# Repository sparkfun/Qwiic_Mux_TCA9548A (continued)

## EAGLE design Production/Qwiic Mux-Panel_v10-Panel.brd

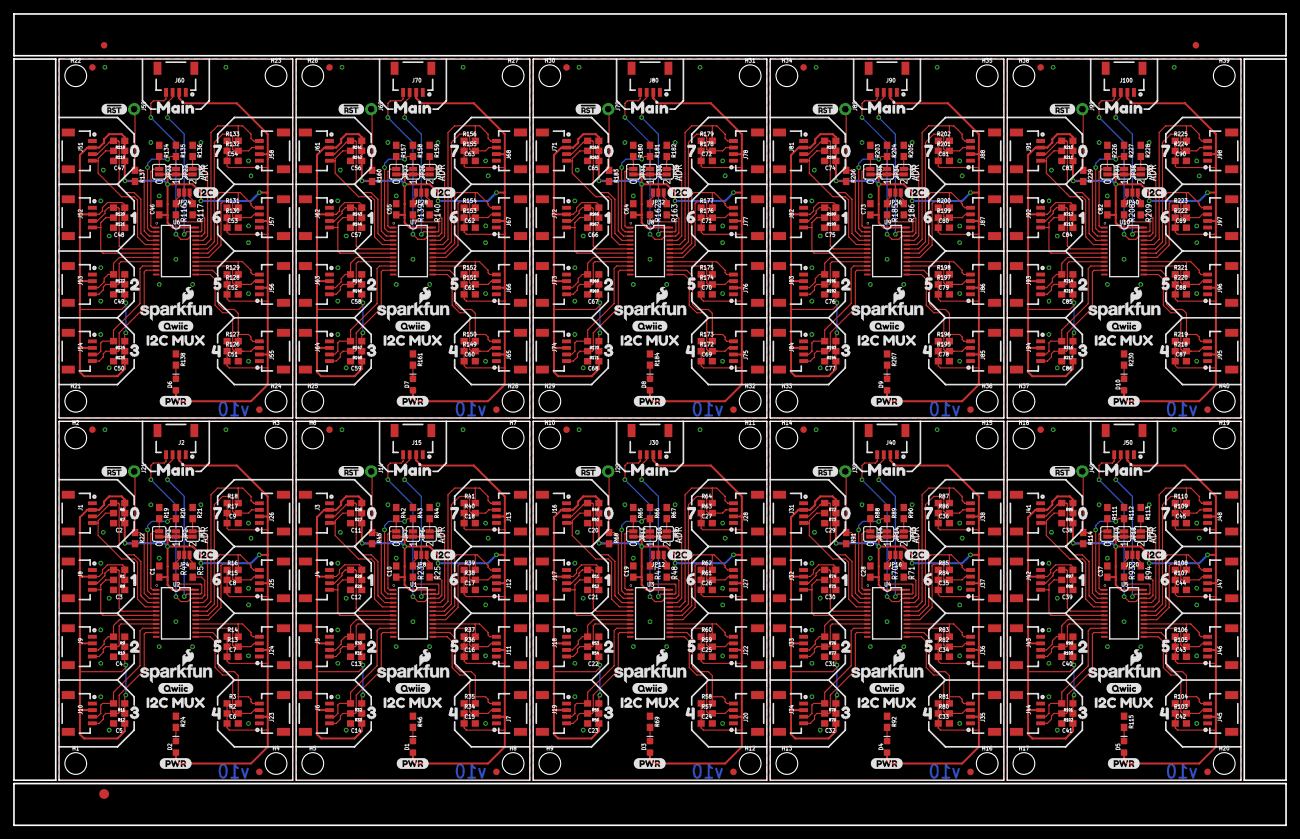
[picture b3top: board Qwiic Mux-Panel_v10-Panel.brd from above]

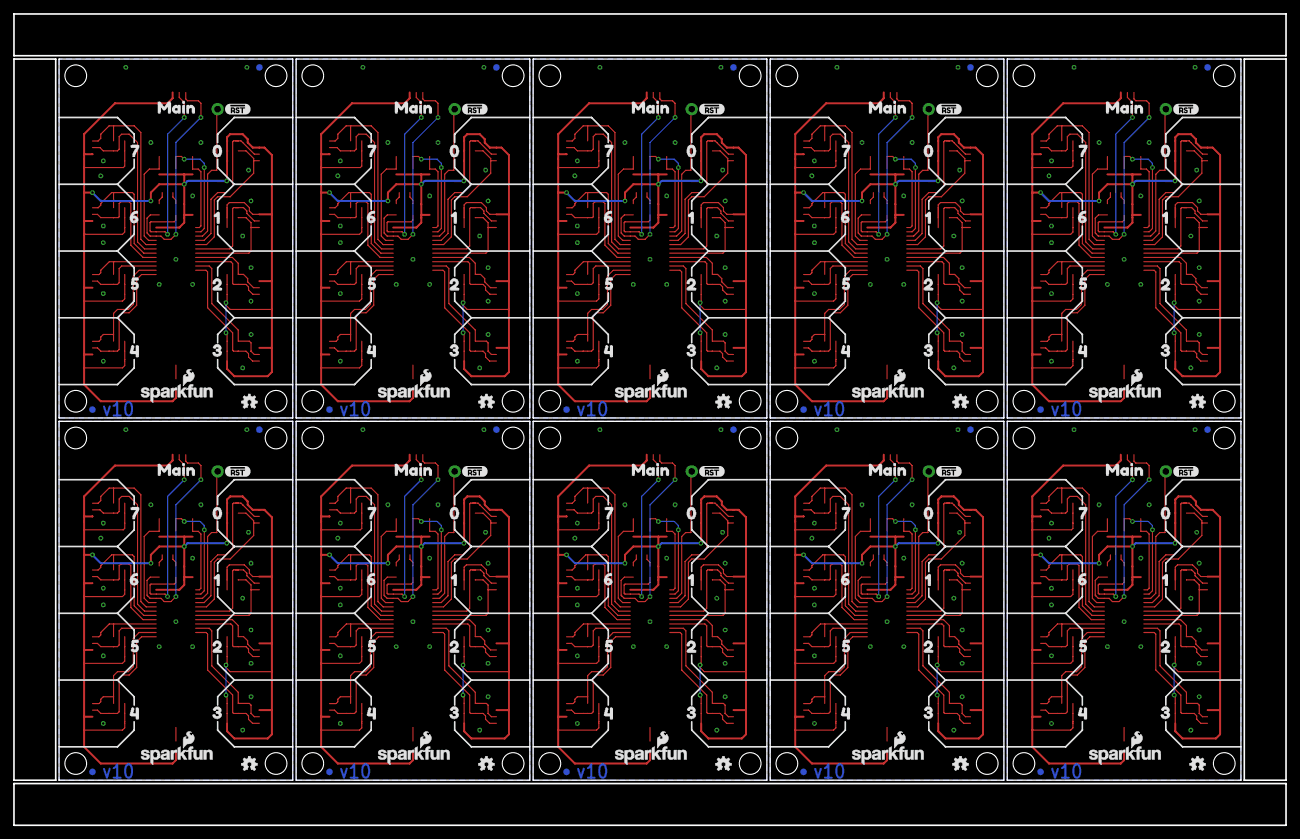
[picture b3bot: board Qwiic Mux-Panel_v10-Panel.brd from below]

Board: 2 copper layers, 193.5 x 123.4 mm, 833 parts (140 on the bottom side), 270 nets.

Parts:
C1, C10, C19, C28, C37, C46, C55, C64, C73, C82: 0.1uF; 0603
C2, C3, C4, C5, C6, C7, C8, C9, C11, C12, C13, C14, C15, C16, C17, C18, C20, C21, C22, C23, C24, C25, C26, C27, C29, C30, C31, C32, C33, C34, C35, C36, C38, C39, C40, C41, C42, C43, C44, C45, C47, C48, C49, C50, C51, C52, C53, C54, C56, C57, C58, C59, C60, C61, C62, C63, C65, C66, C67, C68, C69, C70, C71, C72, C74, C75, C76, C77, C78, C79, C80, C81, C83, C84, C85, C86, C87, C88, C89, C90: 1.0uF; 0603
D1, D2, D3, D4, D5, D6, D7, D8, D9, D10: RED; LED-0603
E$1, E$2: FIDUCIAL-1X2
E$3: FIDUCIAL-1.5X3
FD1, FD2, FD3, FD4, FD5, FD6, FD7, FD8, FD9, FD10, FD11, FD12, FD13, FD14, FD15, FD16, FD17, FD18, FD19, FD20, FD21, FD22, FD23, FD24, FD25, FD26, FD27, FD28, FD29, FD30, FD31, FD32, FD33, FD34, FD35, FD36, FD37, FD38, FD39, FD40: FIDUCIAL1X2; FIDUCIAL-1X2
H1, H2, H3, H4, H5, H6, H7, H8, H9, H10, H11, H12, H13, H14, H15, H16, H17, H18, H19, H20, H21, H22, H23, H24, H25, H26, H27, H28, H29, H30, H31, H32, H33, H34, H35, H36, H37, H38, H39, H40: STAND-OFF
J1, J3, J4, J5, J6, J7, J8, J9, J10, J11, J12, J13, J16, J17, J18, J19, J20, J22, J23, J24, J25, J26, J27, J28, J31, J32, J33, J34, J35, J36, J37, J38, J41, J42, J43, J44, J45, J46, J47, J48, J51, J52, J53, J54, J55, J56, J57, J58, J61, J62, J63, J64, J65, J66, J67, J68, J71, J72, J73, J74, J75, J76, J77, J78, J81, J82, J83, J84, J85, J86, J87, J88, J91, J92, J93, J94, J95, J96, J97, J98: 1X04_1MM_RA
J2, J15, J30, J40, J50, J60, J70, J80, J90, J100: SMD; 1X04_1MM_RA
J14, J21, J29, J39, J49, J59, J69, J79, J89, J99: 1X01_NO_SILK
JP1, JP2, JP3, JP5, JP6, JP7, JP9, JP10, JP11, JP13, JP14, JP15, JP17, JP18, JP19, JP21, JP22, JP23, JP25, JP26, JP27, JP29, JP30, JP31, JP33, JP34, JP35, JP37, JP38, JP39: SMT-JUMPER_2_NO_SILK
JP4, JP8, JP12, JP16, JP20, JP24, JP28, JP32, JP36, JP40: JUMPER-SMT_3_2-NC_PASTE_NO-SILK; SMT-JUMPER_3_2-NC_PASTE_NO-SILK
LOGO1, LOGO2, LOGO3, LOGO4, LOGO5, LOGO6, LOGO7, LOGO8, LOGO9, LOGO10: OSHW-LOGOMINI; OSHW-LOGO-MINI
R1, R2, R3, R4, R5, R6, R7, R8, R9, R10, R11, R12, R13, R14, R15, R16, R17, R18, R23, R25, R26, R27, R28, R29, R30, R31, R32, R33, R34, R35, R36, R37, R38, R39, R40, R41, R47, R48, R49, R50, R51, R52, R53, R54, R55, R56, R57, R58, R59, R60, R61, R62, R63, R64, R70, R71, R72, R73, R74, R75, R76, R77, R78, R79, R80, R81, R82, R83, R84, R85, R86, R87, R93, R94, R95, R96, R97, R98, R99, R100, R101, R102, R103, R104, R105, R106, R107, R108, R109, R110, R116, R117, R118, R119, R120, R121, R122, R123, R124, R125, R126, R127, R128, R129, R130, R131, R132, R133, R139, R140, R141, R142, R143, R144, R145, R146, R147, R148, R149, R150, R151, R152, R153, R154, R155, R156, R162, R163, R164, R165, R166, R167, R168, R169, R170, R171, R172, R173, R174, R175, R176, R177, R178, R179, R185, R186, R187, R188, R189, R190, R191, R192, R193, R194, R195, R196, R197, R198, R199, R200, R201, R202, R208, R209, R210, R211, R212, R213, R214, R215, R216, R217, R218, R219, R220, R221, R222, R223, R224, R225: 4.7k; 0603
R19, R20, R21, R22, R42, R43, R44, R45, R65, R66, R67, R68, R88, R89, R90, R91, R111, R112, R113, R114, R134, R135, R136, R137, R157, R158, R159, R160, R180, R181, R182, R183, R203, R204, R205, R206, R226, R227, R228, R229: 10k; 0603
R24, R46, R69, R92, R115, R138, R161, R184, R207, R230: 1k; 0603
U1, U2, U3, U4, U5, U6, U7, U8, U9, U10: PCA9548A; TSSOP28
U$1, U$2, U$27, U$28, U$53, U$54, U$79, U$80, U$105, U$106, U$131, U$132, U$157, U$158, U$183, U$184, U$209, U$210, U$235, U$236: SFE_LOGO_NAME_FLAME.1_INCH; SFE_LOGO_NAME_FLAME_.1
U$3, U$29, U$55, U$81, U$107, U$133, U$159, U$185, U$211, U$237: (PWR)
U$4, U$30, U$56, U$82, U$108, U$134, U$160, U$186, U$212, U$238: (QWIIC)
U$5, U$31, U$57, U$83, U$109, U$135, U$161, U$187, U$213, U$239: (I2C)
U$6, U$12, U$32, U$43, U$58, U$69, U$84, U$95, U$110, U$121, U$136, U$147, U$162, U$173, U$188, U$199, U$214, U$225, U$240, U$251: 00
U$7, U$18, U$37, U$44, U$63, U$70, U$89, U$96, U$115, U$122, U$141, U$148, U$167, U$174, U$193, U$200, U$219, U$226, U$245, U$252: 11
U$8, U$19, U$38, U$45, U$64, U$71, U$90, U$97, U$116, U$123, U$142, U$149, U$168, U$175, U$194, U$201, U$220, U$227, U$246, U$253: 22
U$9, U$20, U$39, U$46, U$65, U$72, U$91, U$98, U$117, U$124, U$143, U$150, U$169, U$176, U$195, U$202, U$221, U$228, U$247, U$254: 33
U$10, U$21, U$33, U$47, U$59, U$73, U$85, U$99, U$111, U$125, U$137, U$151, U$163, U$177, U$189, U$203, U$215, U$229, U$241, U$255: 44
U$11, U$22, U$34, U$48, U$60, U$74, U$86, U$100, U$112, U$126, U$138, U$152, U$164, U$178, U$190, U$204, U$216, U$230, U$242, U$256: 55
U$13, U$24, U$35, U$50, U$61, U$76, U$87, U$102, U$113, U$128, U$139, U$154, U$165, U$180, U$191, U$206, U$217, U$232, U$243, U$258: 77
U$14, U$26, U$36, U$52, U$62, U$78, U$88, U$104, U$114, U$130, U$140, U$156, U$166, U$182, U$192, U$208, U$218, U$234, U$244, U$260: #RST10
U$15, U$40, U$66, U$92, U$118, U$144, U$170, U$196, U$222, U$248: I2C_MUX8
U$16, U$25, U$41, U$51, U$67, U$77, U$93, U$103, U$119, U$129, U$145, U$155, U$171, U$181, U$197, U$207, U$223, U$233, U$249, U$259: MAIN0
U$17, U$23, U$42, U$49, U$68, U$75, U$94, U$101, U$120, U$127, U$146, U$153, U$172, U$179, U$198, U$205, U$224, U$231, U$250, U$257: 61

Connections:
3.3V: C1.1, C2.1, C3.1, C4.1, C5.1, C6.1, C7.1, C8.1, C9.1, D2.A, J1.2, J2.2, J8.2, J9.2, J10.2, J23.2, J24.2, J25.2, J26.2, JP1.2, JP2.2, JP3.2, JP4.2, R1.1, R2.1, R3.1, R6.1, R7.1, R8.1, R9.1, R10.1, R11.1, R12.1, R13.1, R14.1, R15.1, R16.1, R17.1, R18.1, R22.2, U2.24
3.3V1: C10.1, C11.1, C12.1, C13.1, C14.1, C15.1, C16.1, C17.1, C18.1, D1.A, J3.2, J4.2, J5.2, J6.2, J7.2, J11.2, J12.2, J13.2, J15.2, JP5.2, JP6.2, JP7.2, JP8.2, R26.1, R27.1, R28.1, R29.1, R30.1, R31.1, R32.1, R33.1, R34.1, R35.1, R36.1, R37.1, R38.1, R39.1, R40.1, R41.1, R45.2, U1.24
3.3V2: C19.1, C20.1, C21.1, C22.1, C23.1, C24.1, C25.1, C26.1, C27.1, D3.A, J16.2, J17.2, J18.2, J19.2, J20.2, J22.2, J27.2, J28.2, J30.2, JP9.2, JP10.2, JP11.2, JP12.2, R49.1, R50.1, R51.1, R52.1, R53.1, R54.1, R55.1, R56.1, R57.1, R58.1, R59.1, R60.1, R61.1, R62.1, R63.1, R64.1, R68.2, U3.24
3.3V3: C28.1, C29.1, C30.1, C31.1, C32.1, C33.1, C34.1, C35.1, C36.1, D4.A, J31.2, J32.2, J33.2, J34.2, J35.2, J36.2, J37.2, J38.2, J40.2, JP13.2, JP14.2, JP15.2, JP16.2, R72.1, R73.1, R74.1, R75.1, R76.1, R77.1, R78.1, R79.1, R80.1, R81.1, R82.1, R83.1, R84.1, R85.1, R86.1, R87.1, R91.2, U4.24
3.3V4: C37.1, C38.1, C39.1, C40.1, C41.1, C42.1, C43.1, C44.1, C45.1, D5.A, J41.2, J42.2, J43.2, J44.2, J45.2, J46.2, J47.2, J48.2, J50.2, JP17.2, JP18.2, JP19.2, JP20.2, R95.1, R96.1, R97.1, R98.1, R99.1, R100.1, R101.1, R102.1, R103.1, R104.1, R105.1, R106.1, R107.1, R108.1, R109.1, R110.1, R114.2, U5.24
3.3V5: C46.1, C47.1, C48.1, C49.1, C50.1, C51.1, C52.1, C53.1, C54.1, D6.A, J51.2, J52.2, J53.2, J54.2, J55.2, J56.2, J57.2, J58.2, J60.2, JP21.2, JP22.2, JP23.2, JP24.2, R118.1, R119.1, R120.1, R121.1, R122.1, R123.1, R124.1, R125.1, R126.1, R127.1, R128.1, R129.1, R130.1, R131.1, R132.1, R133.1, R137.2, U6.24
3.3V6: C55.1, C56.1, C57.1, C58.1, C59.1, C60.1, C61.1, C62.1, C63.1, D7.A, J61.2, J62.2, J63.2, J64.2, J65.2, J66.2, J67.2, J68.2, J70.2, JP25.2, JP26.2, JP27.2, JP28.2, R141.1, R142.1, R143.1, R144.1, R145.1, R146.1, R147.1, R148.1, R149.1, R150.1, R151.1, R152.1, R153.1, R154.1, R155.1, R156.1, R160.2, U7.24
3.3V7: C64.1, C65.1, C66.1, C67.1, C68.1, C69.1, C70.1, C71.1, C72.1, D8.A, J71.2, J72.2, J73.2, J74.2, J75.2, J76.2, J77.2, J78.2, J80.2, JP29.2, JP30.2, JP31.2, JP32.2, R164.1, R165.1, R166.1, R167.1, R168.1, R169.1, R170.1, R171.1, R172.1, R173.1, R174.1, R175.1, R176.1, R177.1, R178.1, R179.1, R183.2, U8.24
3.3V8: C73.1, C74.1, C75.1, C76.1, C77.1, C78.1, C79.1, C80.1, C81.1, D9.A, J81.2, J82.2, J83.2, J84.2, J85.2, J86.2, J87.2, J88.2, J90.2, JP33.2, JP34.2, JP35.2, JP36.2, R187.1, R188.1, R189.1, R190.1, R191.1, R192.1, R193.1, R194.1, R195.1, R196.1, R197.1, R198.1, R199.1, R200.1, R201.1, R202.1, R206.2, U9.24
3.3V9: C82.1, C83.1, C84.1, C85.1, C86.1, C87.1, C88.1, C89.1, C90.1, D10.A, J91.2, J92.2, J93.2, J94.2, J95.2, J96.2, J97.2, J98.2, J100.2, JP37.2, JP38.2, JP39.2, JP40.2, R210.1, R211.1, R212.1, R213.1, R214.1, R215.1, R216.1, R217.1, R218.1, R219.1, R220.1, R221.1, R222.1, R223.1, R224.1, R225.1, R229.2, U10.24
!RST: J21.1, R22.1, U2.3
!RST1: J14.1, R45.1, U1.3
!RST2: J29.1, R68.1, U3.3
!RST3: J39.1, R91.1, U4.3
!RST4: J49.1, R114.1, U5.3
!RST5: J59.1, R137.1, U6.3
!RST6: J69.1, R160.1, U7.3
!RST7: J79.1, R183.1, U8.3
!RST8: J89.1, R206.1, U9.3
!RST9: J99.1, R229.1, U10.3
ADR0: JP3.1, R19.2, U2.1
ADR1: JP2.1, R20.2, U2.2
ADR2: JP1.1, R21.2, U2.21
ADR3: JP6.1, R43.2, U1.2
ADR4: JP7.1, R42.2, U1.1
ADR5: JP5.1, R44.2, U1.21
ADR6: JP10.1, R66.2, U3.2
ADR7: JP11.1, R65.2, U3.1
ADR8: JP9.1, R67.2, U3.21
ADR9: JP14.1, R89.2, U4.2
ADR10: JP15.1, R88.2, U4.1
ADR11: JP13.1, R90.2, U4.21
ADR12: JP18.1, R112.2, U5.2
ADR13: JP19.1, R111.2, U5.1
ADR14: JP17.1, R113.2, U5.21
ADR15: JP22.1, R135.2, U6.2
ADR16: JP23.1, R134.2, U6.1
ADR17: JP21.1, R136.2, U6.21
ADR18: JP26.1, R158.2, U7.2
ADR19: JP27.1, R157.2, U7.1
ADR20: JP25.1, R159.2, U7.21
ADR21: JP30.1, R181.2, U8.2
ADR22: JP31.1, R180.2, U8.1
ADR23: JP29.1, R182.2, U8.21
ADR24: JP34.1, R204.2, U9.2
ADR25: JP35.1, R203.2, U9.1
ADR26: JP33.1, R205.2, U9.21
ADR27: JP38.1, R227.2, U10.2
ADR28: JP39.1, R226.2, U10.1
ADR29: JP37.1, R228.2, U10.21
GND: C1.2, C2.2, C3.2, C4.2, C5.2, C6.2, C7.2, C8.2, C9.2, J1.1, J2.1, J8.1, J9.1, J10.1, J23.1, J24.1, J25.1, J26.1, R19.1, R20.1, R21.1, R24.1, U2.12
GND1: C10.2, C11.2, C12.2, C13.2, C14.2, C15.2, C16.2, C17.2, C18.2, J3.1, J4.1, J5.1, J6.1, J7.1, J11.1, J12.1, J13.1, J15.1, R42.1, R43.1, R44.1, R46.1, U1.12
GND2: C19.2, C20.2, C21.2, C22.2, C23.2, C24.2, C25.2, C26.2, C27.2, J16.1, J17.1, J18.1, J19.1, J20.1, J22.1, J27.1, J28.1, J30.1, R65.1, R66.1, R67.1, R69.1, U3.12
GND3: C28.2, C29.2, C30.2, C31.2, C32.2, C33.2, C34.2, C35.2, C36.2, J31.1, J32.1, J33.1, J34.1, J35.1, J36.1, J37.1, J38.1, J40.1, R88.1, R89.1, R90.1, R92.1, U4.12
GND4: C37.2, C38.2, C39.2, C40.2, C41.2, C42.2, C43.2, C44.2, C45.2, J41.1, J42.1, J43.1, J44.1, J45.1, J46.1, J47.1, J48.1, J50.1, R111.1, R112.1, R113.1, R115.1, U5.12
GND5: C46.2, C47.2, C48.2, C49.2, C50.2, C51.2, C52.2, C53.2, C54.2, J51.1, J52.1, J53.1, J54.1, J55.1, J56.1, J57.1, J58.1, J60.1, R134.1, R135.1, R136.1, R138.1, U6.12
GND6: C55.2, C56.2, C57.2, C58.2, C59.2, C60.2, C61.2, C62.2, C63.2, J61.1, J62.1, J63.1, J64.1, J65.1, J66.1, J67.1, J68.1, J70.1, R157.1, R158.1, R159.1, R161.1, U7.12
GND7: C64.2, C65.2, C66.2, C67.2, C68.2, C69.2, C70.2, C71.2, C72.2, J71.1, J72.1, J73.1, J74.1, J75.1, J76.1, J77.1, J78.1, J80.1, R180.1, R181.1, R182.1, R184.1, U8.12
GND8: C73.2, C74.2, C75.2, C76.2, C77.2, C78.2, C79.2, C80.2, C81.2, J81.1, J82.1, J83.1, J84.1, J85.1, J86.1, J87.1, J88.1, J90.1, R203.1, R204.1, R205.1, R207.1, U9.12
GND9: C82.2, C83.2, C84.2, C85.2, C86.2, C87.2, C88.2, C89.2, C90.2, J91.1, J92.1, J93.1, J94.1, J95.1, J96.1, J97.1, J98.1, J100.1, R226.1, R227.1, R228.1, R230.1, U10.12
MAIN_SCL: J2.4, R5.2, U2.22
MAIN_SCL1: J15.4, R25.2, U1.22
MAIN_SCL2: J30.4, R48.2, U3.22
MAIN_SCL3: J40.4, R71.2, U4.22
MAIN_SCL4: J50.4, R94.2, U5.22
MAIN_SCL5: J60.4, R117.2, U6.22
MAIN_SCL6: J70.4, R140.2, U7.22
MAIN_SCL7: J80.4, R163.2, U8.22
MAIN_SCL8: J90.4, R186.2, U9.22
MAIN_SCL9: J100.4, R209.2, U10.22
MAIN_SDA: J2.3, R4.2, U2.23
MAIN_SDA1: J15.3, R23.2, U1.23
MAIN_SDA2: J30.3, R47.2, U3.23
MAIN_SDA3: J40.3, R70.2, U4.23
MAIN_SDA4: J50.3, R93.2, U5.23
MAIN_SDA5: J60.3, R116.2, U6.23
MAIN_SDA6: J70.3, R139.2, U7.23
MAIN_SDA7: J80.3, R162.2, U8.23
MAIN_SDA8: J90.3, R185.2, U9.23
MAIN_SDA9: J100.3, R208.2, U10.23
unnamed: D2.C, R24.2
unnamed: JP4.3, R4.1
unnamed: JP4.1, R5.1
unnamed: D1.C, R46.2
unnamed: JP8.3, R23.1
unnamed: JP8.1, R25.1
unnamed: D3.C, R69.2
unnamed: JP12.3, R47.1
unnamed: JP12.1, R48.1
unnamed: D4.C, R92.2
unnamed: JP16.3, R70.1
unnamed: JP16.1, R71.1
unnamed: D5.C, R115.2
unnamed: JP20.3, R93.1
unnamed: JP20.1, R94.1
unnamed: D6.C, R138.2
unnamed: JP24.3, R116.1
unnamed: JP24.1, R117.1
unnamed: D7.C, R161.2
unnamed: JP28.3, R139.1
unnamed: JP28.1, R140.1
unnamed: D8.C, R184.2
unnamed: JP32.3, R162.1
unnamed: JP32.1, R163.1
unnamed: D9.C, R207.2
unnamed: JP36.3, R185.1
unnamed: JP36.1, R186.1
unnamed: D10.C, R230.2
unnamed: JP40.3, R208.1
unnamed: JP40.1, R209.1
SCL0: J1.4, R7.2, U2.5
SCL1: J8.4, R8.2, U2.7
SCL2: J9.4, R10.2, U2.9
SCL3: J10.4, R12.2, U2.11
SCL4: J23.4, R3.2, U2.14
SCL5: J24.4, R14.2, U2.16
SCL6: J25.4, R16.2, U2.18
SCL7: J26.4, R18.2, U2.20
SCL8: J3.4, R27.2, U1.5
SCL9: J4.4, R29.2, U1.7
SCL10: J6.4, R33.2, U1.11
SCL11: J7.4, R35.2, U1.14
SCL12: J11.4, R37.2, U1.16
SCL13: J12.4, R39.2, U1.18
SCL14: J13.4, R41.2, U1.20
SCL15: J5.4, R31.2, U1.9
SCL16: J16.4, R50.2, U3.5
SCL17: J17.4, R52.2, U3.7
SCL18: J19.4, R56.2, U3.11
SCL19: J20.4, R58.2, U3.14
SCL20: J22.4, R60.2, U3.16
SCL21: J27.4, R62.2, U3.18
SCL22: J28.4, R64.2, U3.20
SCL23: J18.4, R54.2, U3.9
SCL24: J31.4, R73.2, U4.5
SCL25: J32.4, R75.2, U4.7
SCL26: J34.4, R79.2, U4.11
SCL27: J35.4, R81.2, U4.14
SCL28: J36.4, R83.2, U4.16
SCL29: J37.4, R85.2, U4.18
SCL30: J38.4, R87.2, U4.20
SCL31: J33.4, R77.2, U4.9
SCL32: J41.4, R96.2, U5.5
SCL33: J42.4, R98.2, U5.7
SCL34: J44.4, R102.2, U5.11
SCL35: J45.4, R104.2, U5.14
SCL36: J46.4, R106.2, U5.16
SCL37: J47.4, R108.2, U5.18
SCL38: J48.4, R110.2, U5.20
SCL39: J43.4, R100.2, U5.9
SCL40: J51.4, R119.2, U6.5
SCL41: J52.4, R121.2, U6.7
SCL42: J54.4, R125.2, U6.11
SCL43: J55.4, R127.2, U6.14
SCL44: J56.4, R129.2, U6.16
SCL45: J57.4, R131.2, U6.18
SCL46: J58.4, R133.2, U6.20
SCL47: J53.4, R123.2, U6.9
SCL48: J61.4, R142.2, U7.5
SCL49: J62.4, R144.2, U7.7
SCL50: J64.4, R148.2, U7.11
SCL51: J65.4, R150.2, U7.14
SCL52: J66.4, R152.2, U7.16
SCL53: J67.4, R154.2, U7.18
SCL54: J68.4, R156.2, U7.20
SCL55: J63.4, R146.2, U7.9
SCL56: J71.4, R165.2, U8.5
SCL57: J72.4, R167.2, U8.7
SCL58: J74.4, R171.2, U8.11
SCL59: J75.4, R173.2, U8.14
SCL60: J76.4, R175.2, U8.16
SCL61: J77.4, R177.2, U8.18
SCL62: J78.4, R179.2, U8.20
SCL63: J73.4, R169.2, U8.9
SCL64: J81.4, R188.2, U9.5
SCL65: J82.4, R190.2, U9.7
SCL66: J84.4, R194.2, U9.11
SCL67: J85.4, R196.2, U9.14
SCL68: J86.4, R198.2, U9.16
SCL69: J87.4, R200.2, U9.18
SCL70: J88.4, R202.2, U9.20
SCL71: J83.4, R192.2, U9.9
SCL72: J91.4, R211.2, U10.5
SCL73: J92.4, R213.2, U10.7
SCL74: J94.4, R217.2, U10.11
SCL75: J95.4, R219.2, U10.14
SCL76: J96.4, R221.2, U10.16
SCL77: J97.4, R223.2, U10.18
SCL78: J98.4, R225.2, U10.20
SCL79: J93.4, R215.2, U10.9
SDA0: J1.3, R6.2, U2.4
SDA1: J8.3, R1.2, U2.6
SDA2: J9.3, R9.2, U2.8
SDA3: J10.3, R11.2, U2.10
SDA4: J23.3, R2.2, U2.13
SDA5: J24.3, R13.2, U2.15
SDA6: J25.3, R15.2, U2.17
SDA7: J26.3, R17.2, U2.19
SDA8: J3.3, R26.2, U1.4
SDA9: J4.3, R28.2, U1.6
SDA10: J6.3, R32.2, U1.10
SDA11: J7.3, R34.2, U1.13
SDA12: J11.3, R36.2, U1.15
SDA13: J13.3, R40.2, U1.19
SDA14: J12.3, R38.2, U1.17
SDA15: J5.3, R30.2, U1.8
SDA16: J16.3, R49.2, U3.4
SDA17: J17.3, R51.2, U3.6
SDA18: J19.3, R55.2, U3.10
SDA19: J20.3, R57.2, U3.13
SDA20: J22.3, R59.2, U3.15
SDA21: J28.3, R63.2, U3.19
SDA22: J27.3, R61.2, U3.17
SDA23: J18.3, R53.2, U3.8
SDA24: J31.3, R72.2, U4.4
SDA25: J32.3, R74.2, U4.6
SDA26: J34.3, R78.2, U4.10
SDA27: J35.3, R80.2, U4.13
SDA28: J36.3, R82.2, U4.15
SDA29: J38.3, R86.2, U4.19
SDA30: J37.3, R84.2, U4.17
SDA31: J33.3, R76.2, U4.8
SDA32: J41.3, R95.2, U5.4
SDA33: J42.3, R97.2, U5.6
SDA34: J44.3, R101.2, U5.10
SDA35: J45.3, R103.2, U5.13
SDA36: J46.3, R105.2, U5.15
SDA37: J48.3, R109.2, U5.19
SDA38: J47.3, R107.2, U5.17
SDA39: J43.3, R99.2, U5.8
SDA40: J51.3, R118.2, U6.4
SDA41: J52.3, R120.2, U6.6
SDA42: J54.3, R124.2, U6.10
SDA43: J55.3, R126.2, U6.13
SDA44: J56.3, R128.2, U6.15
SDA45: J58.3, R132.2, U6.19
SDA46: J57.3, R130.2, U6.17
SDA47: J53.3, R122.2, U6.8
SDA48: J61.3, R141.2, U7.4
SDA49: J62.3, R143.2, U7.6
SDA50: J64.3, R147.2, U7.10
SDA51: J65.3, R149.2, U7.13
SDA52: J66.3, R151.2, U7.15
SDA53: J68.3, R155.2, U7.19
SDA54: J67.3, R153.2, U7.17
SDA55: J63.3, R145.2, U7.8
SDA56: J71.3, R164.2, U8.4
SDA57: J72.3, R166.2, U8.6
SDA58: J74.3, R170.2, U8.10
SDA59: J75.3, R172.2, U8.13
SDA60: J76.3, R174.2, U8.15
SDA61: J78.3, R178.2, U8.19
SDA62: J77.3, R176.2, U8.17
SDA63: J73.3, R168.2, U8.8
SDA64: J81.3, R187.2, U9.4
SDA65: J82.3, R189.2, U9.6
SDA66: J84.3, R193.2, U9.10
SDA67: J85.3, R195.2, U9.13
SDA68: J86.3, R197.2, U9.15
SDA69: J88.3, R201.2, U9.19
SDA70: J87.3, R199.2, U9.17
SDA71: J83.3, R191.2, U9.8
SDA72: J91.3, R210.2, U10.4
SDA73: J92.3, R212.2, U10.6
SDA74: J94.3, R216.2, U10.10
SDA75: J95.3, R218.2, U10.13
SDA76: J96.3, R220.2, U10.15
SDA77: J98.3, R224.2, U10.19
SDA78: J97.3, R222.2, U10.17
SDA79: J93.3, R214.2, U10.8

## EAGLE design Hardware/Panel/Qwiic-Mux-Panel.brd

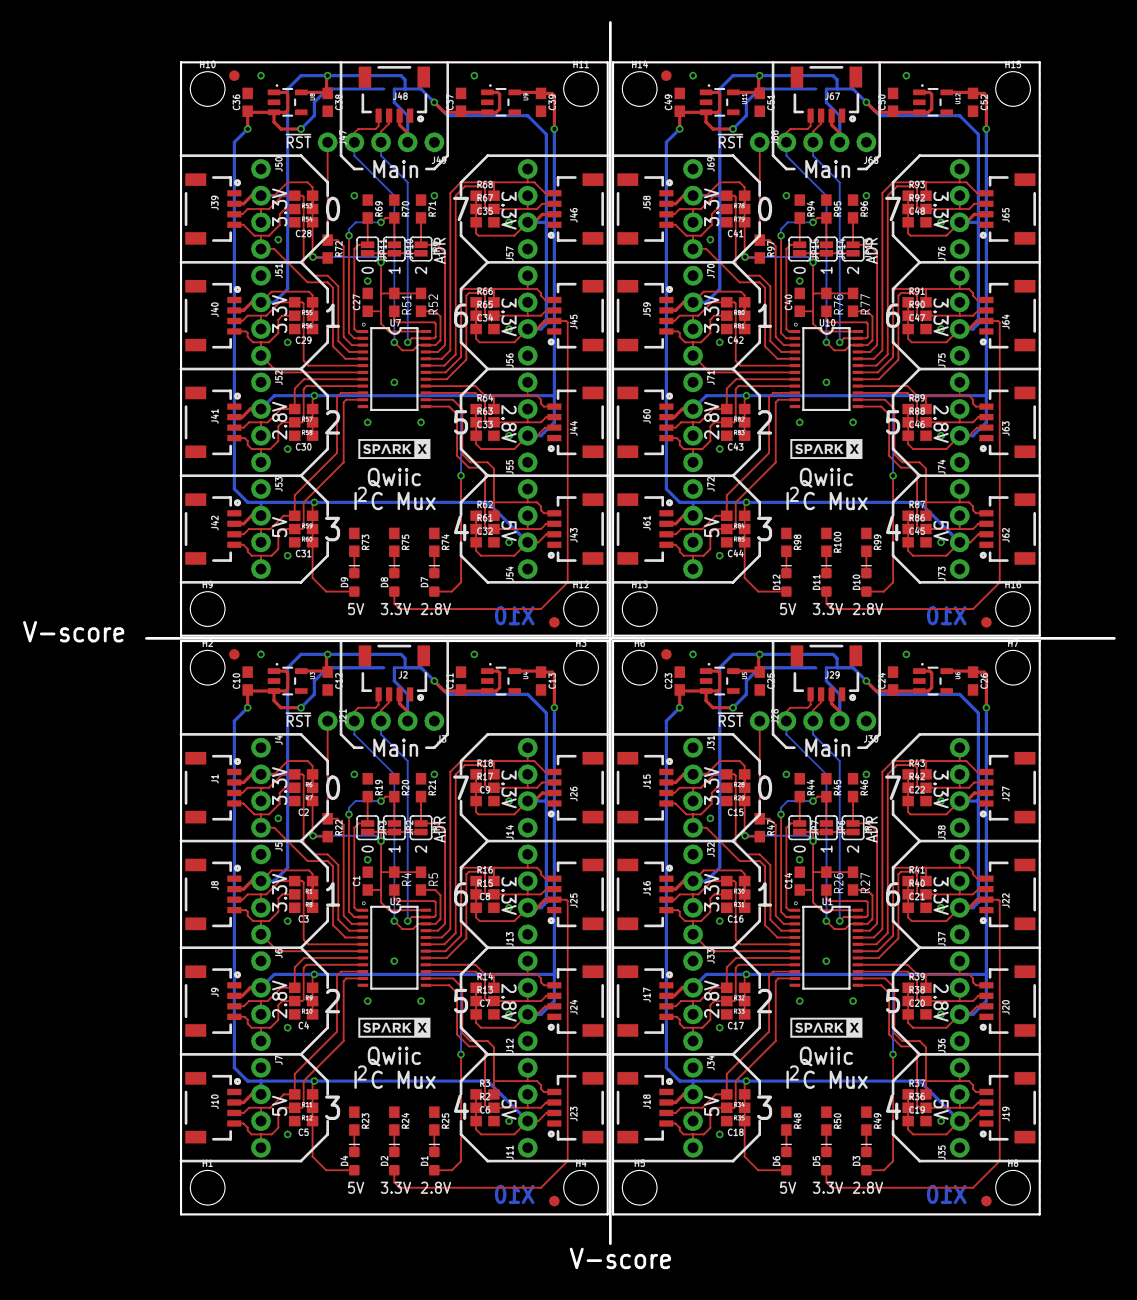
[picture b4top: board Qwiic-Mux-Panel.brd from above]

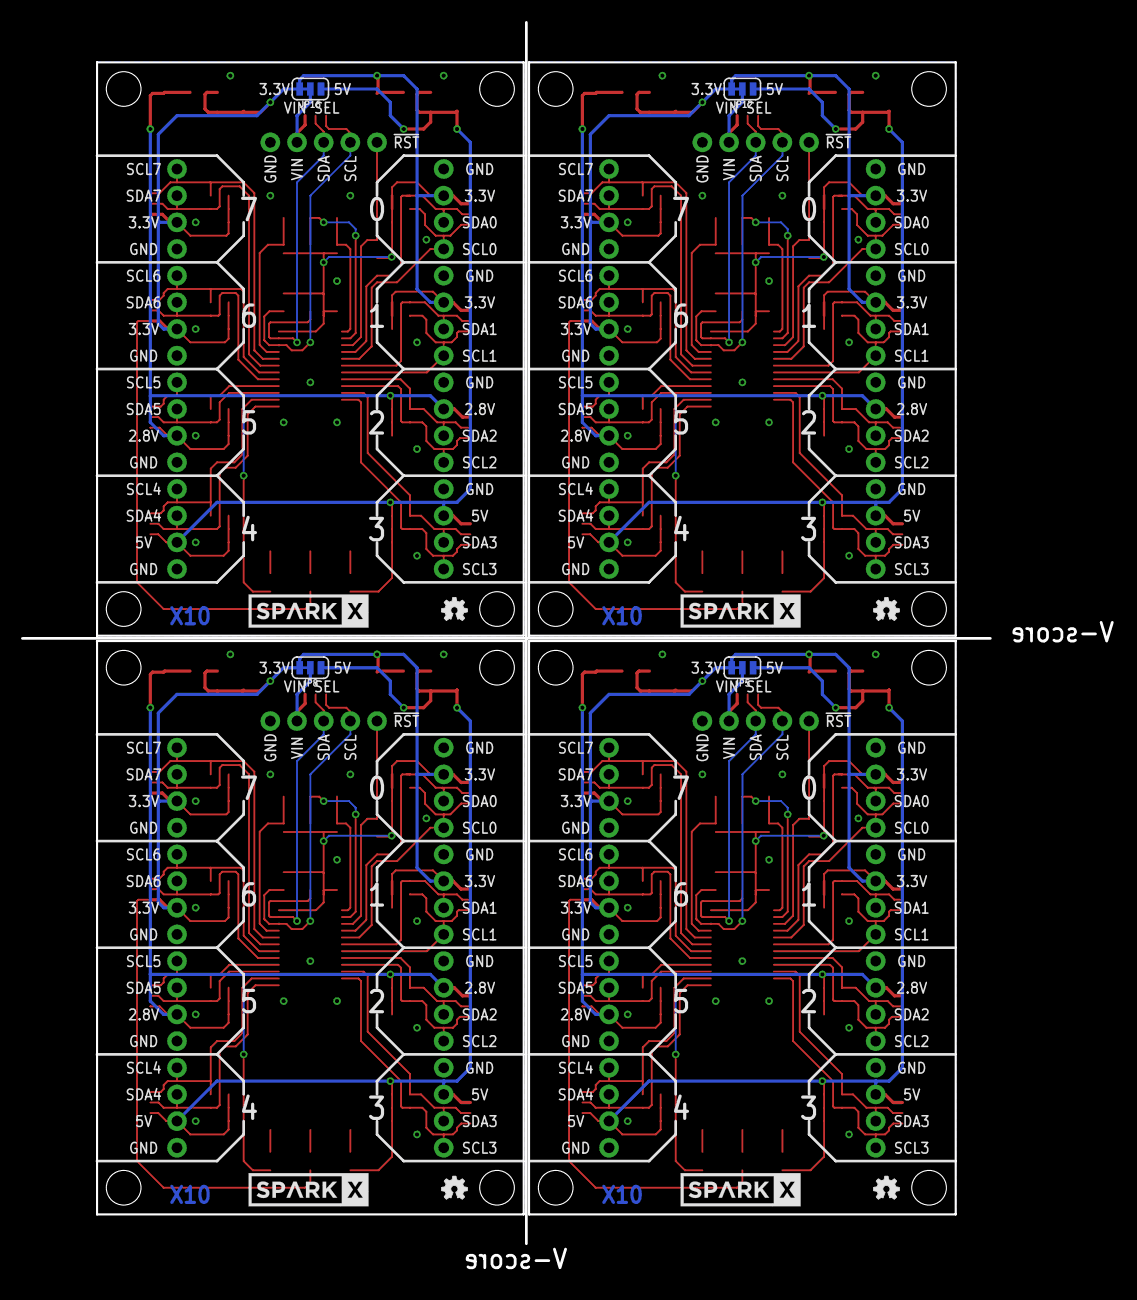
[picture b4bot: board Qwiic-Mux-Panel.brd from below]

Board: 2 copper layers, 104.0 x 119.6 mm, 304 parts (12 on the bottom side), 120 nets.

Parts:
C1, C14, C27, C40: 0.1uF; 0603
C2, C3, C4, C5, C6, C7, C8, C9, C12, C15, C16, C17, C18, C19, C20, C21, C22, C25, C28, C29, C30, C31, C32, C33, C34, C35, C38, C41, C42, C43, C44, C45, C46, C47, C48, C51: 1.0uF; 0603
C10, C11, C13, C23, C24, C26, C36, C37, C39, C49, C50, C52: 10uF; 0603
D1, D3, D7, D10: GREEN; LED-0603
D2, D5, D8, D11: Yellow; LED-0603
D4, D6, D9, D12: BLUE; LED-0603
FD1, FD2, FD3, FD4, FD5, FD6, FD7, FD8: FIDUCIAL1X2; FIDUCIAL-1X2
H1, H2, H3, H4, H5, H6, H7, H8, H9, H10, H11, H12, H13, H14, H15, H16: STAND-OFF
J1, J2, J8, J9, J10, J15, J16, J17, J18, J19, J20, J22, J23, J24, J25, J26, J27, J29, J39, J40, J41, J42, J43, J44, J45, J46, J48, J58, J59, J60, J61, J62, J63, J64, J65, J67: SMD; 1X04_1MM_RA
J3, J4, J5, J6, J7, J11, J12, J13, J14, J30, J31, J32, J33, J34, J35, J36, J37, J38, J49, J50, J51, J52, J53, J54, J55, J56, J57, J68, J69, J70, J71, J72, J73, J74, J75, J76: PTH; 1X04_NO_SILK
J21, J28, J47, J66: 1X01_NO_SILK
JP1, JP2, JP3, JP4, JP6, JP7, JP9, JP10, JP11, JP13, JP14, JP15: SMT-JUMPER_2_NO_SILK
JP5, JP8, JP12, JP16: SMT-JUMPER_3_1-NC_TRACE_SILK
LOGO1, LOGO2, LOGO3, LOGO4: OSHW-LOGOMINI; OSHW-LOGO-MINI
R1, R2, R3, R4, R5, R6, R7, R8, R9, R10, R11, R12, R13, R14, R15, R16, R17, R18, R26, R27, R28, R29, R30, R31, R32, R33, R34, R35, R36, R37, R38, R39, R40, R41, R42, R43, R51, R52, R53, R54, R55, R56, R57, R58, R59, R60, R61, R62, R63, R64, R65, R66, R67, R68, R76, R77, R78, R79, R80, R81, R82, R83, R84, R85, R86, R87, R88, R89, R90, R91, R92, R93: 4.7k; 0603
R19, R20, R21, R22, R44, R45, R46, R47, R69, R70, R71, R72, R94, R95, R96, R97: 10k; 0603
R23, R24, R25, R48, R49, R50, R73, R74, R75, R98, R99, R100: 330; 0603
U1, U2, U7, U10: TCA9548A; TSSOP28
U3, U5, U8, U11: 3.3V/150mA; SOT23-5
U4, U6, U9, U12: 2.8V/150mA; SOT23-5
U$1, U$3, U$5, U$7: SPARKX-LOGO3; SPARKX-SMALL
U$2, U$4, U$6, U$8: SPARKX-LOGO5; SPARKX-LARGE

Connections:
2.8V: C4.1, C7.1, C13.1, D1.A, J6.2, J9.2, J12.2, J24.2, R9.1, R10.1, R13.1, R14.1, U4.5
2.8V1: C17.1, C20.1, C26.1, D3.A, J17.2, J20.2, J33.2, J36.2, R32.1, R33.1, R38.1, R39.1, U6.5
2.8V2: C30.1, C33.1, C39.1, D7.A, J41.2, J44.2, J52.2, J55.2, R57.1, R58.1, R63.1, R64.1, U9.5
2.8V3: C43.1, C46.1, C52.1, D10.A, J60.2, J63.2, J71.2, J74.2, R82.1, R83.1, R88.1, R89.1, U12.5
3.3V: C1.1, C2.1, C3.1, C8.1, C9.1, C11.1, C12.1, D2.A, J1.2, J4.2, J5.2, J8.2, J13.2, J14.2, J25.2, J26.2, JP1.2, JP2.2, JP3.2, JP5.3, R1.1, R4.1, R5.1, R6.1, R7.1, R8.1, R15.1, R16.1, R17.1, R18.1, R22.2, U2.24, U3.5, U4.1, U4.3
3.3V1: C14.1, C15.1, C16.1, C21.1, C22.1, C24.1, C25.1, D5.A, J15.2, J16.2, J22.2, J27.2, J31.2, J32.2, J37.2, J38.2, JP4.2, JP6.2, JP7.2, JP8.3, R26.1, R27.1, R28.1, R29.1, R30.1, R31.1, R40.1, R41.1, R42.1, R43.1, R47.2, U1.24, U5.5, U6.1, U6.3
3.3V2: C27.1, C28.1, C29.1, C34.1, C35.1, C37.1, C38.1, D8.A, J39.2, J40.2, J45.2, J46.2, J50.2, J51.2, J56.2, J57.2, JP9.2, JP10.2, JP11.2, JP12.3, R51.1, R52.1, R53.1, R54.1, R55.1, R56.1, R65.1, R66.1, R67.1, R68.1, R72.2, U7.24, U8.5, U9.1, U9.3
3.3V3: C40.1, C41.1, C42.1, C47.1, C48.1, C50.1, C51.1, D11.A, J58.2, J59.2, J64.2, J65.2, J69.2, J70.2, J75.2, J76.2, JP13.2, JP14.2, JP15.2, JP16.3, R76.1, R77.1, R78.1, R79.1, R80.1, R81.1, R90.1, R91.1, R92.1, R93.1, R97.2, U10.24, U11.5, U12.1, U12.3
5V: C5.1, C6.1, C10.1, D4.A, J7.2, J10.2, J11.2, J23.2, JP5.1, R2.1, R3.1, R11.1, R12.1, U3.1, U3.3
5V1: C18.1, C19.1, C23.1, D6.A, J18.2, J19.2, J34.2, J35.2, JP8.1, R34.1, R35.1, R36.1, R37.1, U5.1, U5.3
5V2: C31.1, C32.1, C36.1, D9.A, J42.2, J43.2, J53.2, J54.2, JP12.1, R59.1, R60.1, R61.1, R62.1, U8.1, U8.3
5V3: C44.1, C45.1, C49.1, D12.A, J61.2, J62.2, J72.2, J73.2, JP16.1, R84.1, R85.1, R86.1, R87.1, U11.1, U11.3
!RST: J21.1, R22.1, U2.3
!RST1: J28.1, R47.1, U1.3
!RST2: J47.1, R72.1, U7.3
!RST3: J66.1, R97.1, U10.3
ADR0: JP3.1, R19.2, U2.1
ADR1: JP2.1, R20.2, U2.2
ADR2: JP1.1, R21.2, U2.21
ADR3: JP6.1, R45.2, U1.2
ADR4: JP7.1, R44.2, U1.1
ADR5: JP4.1, R46.2, U1.21
ADR6: JP10.1, R70.2, U7.2
ADR7: JP11.1, R69.2, U7.1
ADR8: JP9.1, R71.2, U7.21
ADR9: JP14.1, R95.2, U10.2
ADR10: JP15.1, R94.2, U10.1
ADR11: JP13.1, R96.2, U10.21
GND: C1.2, C2.2, C3.2, C4.2, C5.2, C6.2, C7.2, C8.2, C9.2, C10.2, C11.2, C12.2, C13.2, J1.1, J2.1, J3.1, J4.1, J5.1, J6.1, J7.1, J8.1, J9.1, J10.1, J11.1, J12.1, J13.1, J14.1, J23.1, J24.1, J25.1, J26.1, R19.1, R20.1, R21.1, R23.1, R24.1, R25.1, U2.12, U3.2, U4.2
GND1: C14.2, C15.2, C16.2, C17.2, C18.2, C19.2, C20.2, C21.2, C22.2, C23.2, C24.2, C25.2, C26.2, J15.1, J16.1, J17.1, J18.1, J19.1, J20.1, J22.1, J27.1, J29.1, J30.1, J31.1, J32.1, J33.1, J34.1, J35.1, J36.1, J37.1, J38.1, R44.1, R45.1, R46.1, R48.1, R49.1, R50.1, U1.12, U5.2, U6.2
GND2: C27.2, C28.2, C29.2, C30.2, C31.2, C32.2, C33.2, C34.2, C35.2, C36.2, C37.2, C38.2, C39.2, J39.1, J40.1, J41.1, J42.1, J43.1, J44.1, J45.1, J46.1, J48.1, J49.1, J50.1, J51.1, J52.1, J53.1, J54.1, J55.1, J56.1, J57.1, R69.1, R70.1, R71.1, R73.1, R74.1, R75.1, U7.12, U8.2, U9.2
GND3: C40.2, C41.2, C42.2, C43.2, C44.2, C45.2, C46.2, C47.2, C48.2, C49.2, C50.2, C51.2, C52.2, J58.1, J59.1, J60.1, J61.1, J62.1, J63.1, J64.1, J65.1, J67.1, J68.1, J69.1, J70.1, J71.1, J72.1, J73.1, J74.1, J75.1, J76.1, R94.1, R95.1, R96.1, R98.1, R99.1, R100.1, U10.12, U11.2, U12.2
MAIN_SCL: J2.4, J3.4, R5.2, U2.22
MAIN_SCL1: J29.4, J30.4, R27.2, U1.22
MAIN_SCL2: J48.4, J49.4, R52.2, U7.22
MAIN_SCL3: J67.4, J68.4, R77.2, U10.22
MAIN_SDA: J2.3, J3.3, R4.2, U2.23
MAIN_SDA1: J29.3, J30.3, R26.2, U1.23
MAIN_SDA2: J48.3, J49.3, R51.2, U7.23
MAIN_SDA3: J67.3, J68.3, R76.2, U10.23
unnamed: D2.C, R24.2
unnamed: D5.C, R50.2
unnamed: D1.C, R25.2
unnamed: D4.C, R23.2
unnamed: D3.C, R49.2
unnamed: D6.C, R48.2
unnamed: D8.C, R75.2
unnamed: D7.C, R74.2
unnamed: D9.C, R73.2
unnamed: D11.C, R100.2
unnamed: D10.C, R99.2
unnamed: D12.C, R98.2
SCL0: J1.4, J4.4, R7.2, U2.5
SCL1: J5.4, J8.4, R8.2, U2.7
SCL2: J6.4, J9.4, R10.2, U2.9
SCL3: J7.4, J10.4, R12.2, U2.11
SCL4: J11.4, J23.4, R3.2, U2.14
SCL5: J12.4, J24.4, R14.2, U2.16
SCL6: J13.4, J25.4, R16.2, U2.18
SCL7: J14.4, J26.4, R18.2, U2.20
SCL8: J15.4, J31.4, R29.2, U1.5
SCL9: J16.4, J32.4, R31.2, U1.7
SCL10: J18.4, J34.4, R35.2, U1.11
SCL11: J19.4, J35.4, R37.2, U1.14
SCL12: J20.4, J36.4, R39.2, U1.16
SCL13: J22.4, J37.4, R41.2, U1.18
SCL14: J27.4, J38.4, R43.2, U1.20
SCL15: J17.4, J33.4, R33.2, U1.9
SCL16: J39.4, J50.4, R54.2, U7.5
SCL17: J40.4, J51.4, R56.2, U7.7
SCL18: J42.4, J53.4, R60.2, U7.11
SCL19: J43.4, J54.4, R62.2, U7.14
SCL20: J44.4, J55.4, R64.2, U7.16
SCL21: J45.4, J56.4, R66.2, U7.18
SCL22: J46.4, J57.4, R68.2, U7.20
SCL23: J41.4, J52.4, R58.2, U7.9
SCL24: J58.4, J69.4, R79.2, U10.5
SCL25: J59.4, J70.4, R81.2, U10.7
SCL26: J61.4, J72.4, R85.2, U10.11
SCL27: J62.4, J73.4, R87.2, U10.14
SCL28: J63.4, J74.4, R89.2, U10.16
SCL29: J64.4, J75.4, R91.2, U10.18
SCL30: J65.4, J76.4, R93.2, U10.20
SCL31: J60.4, J71.4, R83.2, U10.9
SDA0: J1.3, J4.3, R6.2, U2.4
SDA1: J5.3, J8.3, R1.2, U2.6
SDA2: J6.3, J9.3, R9.2, U2.8
SDA3: J7.3, J10.3, R11.2, U2.10
SDA4: J11.3, J23.3, R2.2, U2.13
SDA5: J12.3, J24.3, R13.2, U2.15
SDA6: J13.3, J25.3, R15.2, U2.17
SDA7: J14.3, J26.3, R17.2, U2.19
SDA8: J15.3, J31.3, R28.2, U1.4
SDA9: J16.3, J32.3, R30.2, U1.6
SDA10: J18.3, J34.3, R34.2, U1.10
SDA11: J19.3, J35.3, R36.2, U1.13
SDA12: J20.3, J36.3, R38.2, U1.15
SDA13: J27.3, J38.3, R42.2, U1.19
SDA14: J22.3, J37.3, R40.2, U1.17
SDA15: J17.3, J33.3, R32.2, U1.8
SDA16: J39.3, J50.3, R53.2, U7.4
SDA17: J40.3, J51.3, R55.2, U7.6
SDA18: J42.3, J53.3, R59.2, U7.10
SDA19: J43.3, J54.3, R61.2, U7.13
SDA20: J44.3, J55.3, R63.2, U7.15
SDA21: J46.3, J57.3, R67.2, U7.19
SDA22: J45.3, J56.3, R65.2, U7.17
SDA23: J41.3, J52.3, R57.2, U7.8
SDA24: J58.3, J69.3, R78.2, U10.4
SDA25: J59.3, J70.3, R80.2, U10.6
SDA26: J61.3, J72.3, R84.2, U10.10
SDA27: J62.3, J73.3, R86.2, U10.13
SDA28: J63.3, J74.3, R88.2, U10.15
SDA29: J65.3, J76.3, R92.2, U10.19
SDA30: J64.3, J75.3, R90.2, U10.17
SDA31: J60.3, J71.3, R82.2, U10.8
VIN: J2.2, J3.2, JP5.2
VIN1: J29.2, J30.2, JP8.2
VIN2: J48.2, J49.2, JP12.2
VIN3: J67.2, J68.2, JP16.2

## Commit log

2018-04-17 Post design Review Changes
2018-05-21 gerbers
2018-05-23 checklist changes
2018-05-29 Updated Qwiic connector
2018-05-30 created panel v10
2019-12-28 Update Board
    Add second "Main" Qwiic connector
2019-12-30 Fix routing and version numbering
2020-02-28 Update Qwiic Mux.brd
    Fix trace thickness
2020-05-17 Update Qwiic label. Update labels on ADR and RESET pins.
2020-05-19 creating panel v11
2020-07-01 Update README.md
    comment blocks for v2
2020-07-01 Update README.md
    Fix title
2020-07-02 Update README.md
    Updated product release
2020-07-02 Update README.md
    Fix version and naming
